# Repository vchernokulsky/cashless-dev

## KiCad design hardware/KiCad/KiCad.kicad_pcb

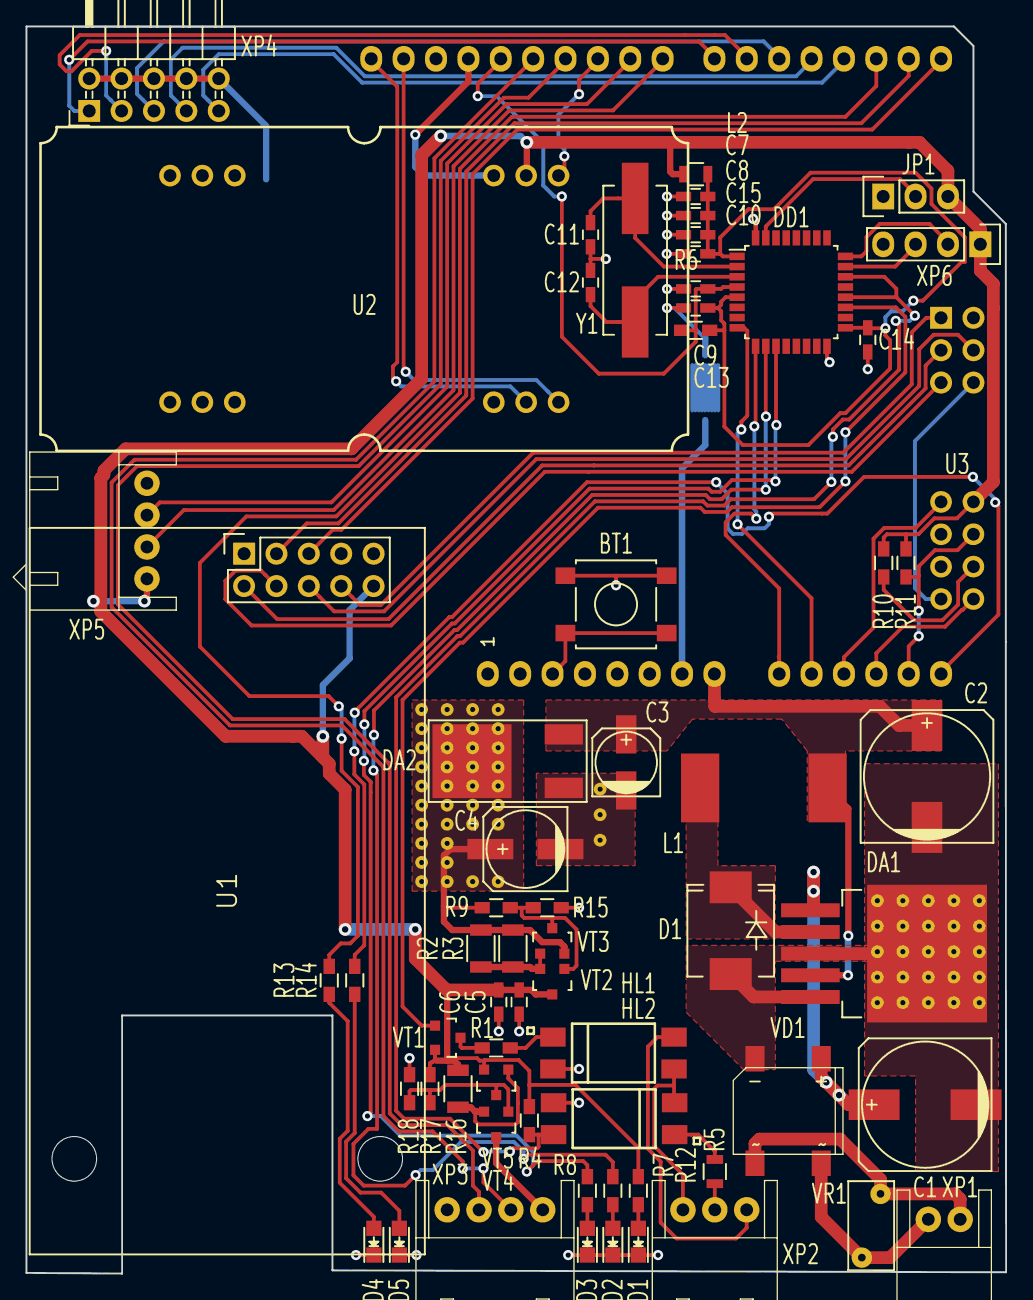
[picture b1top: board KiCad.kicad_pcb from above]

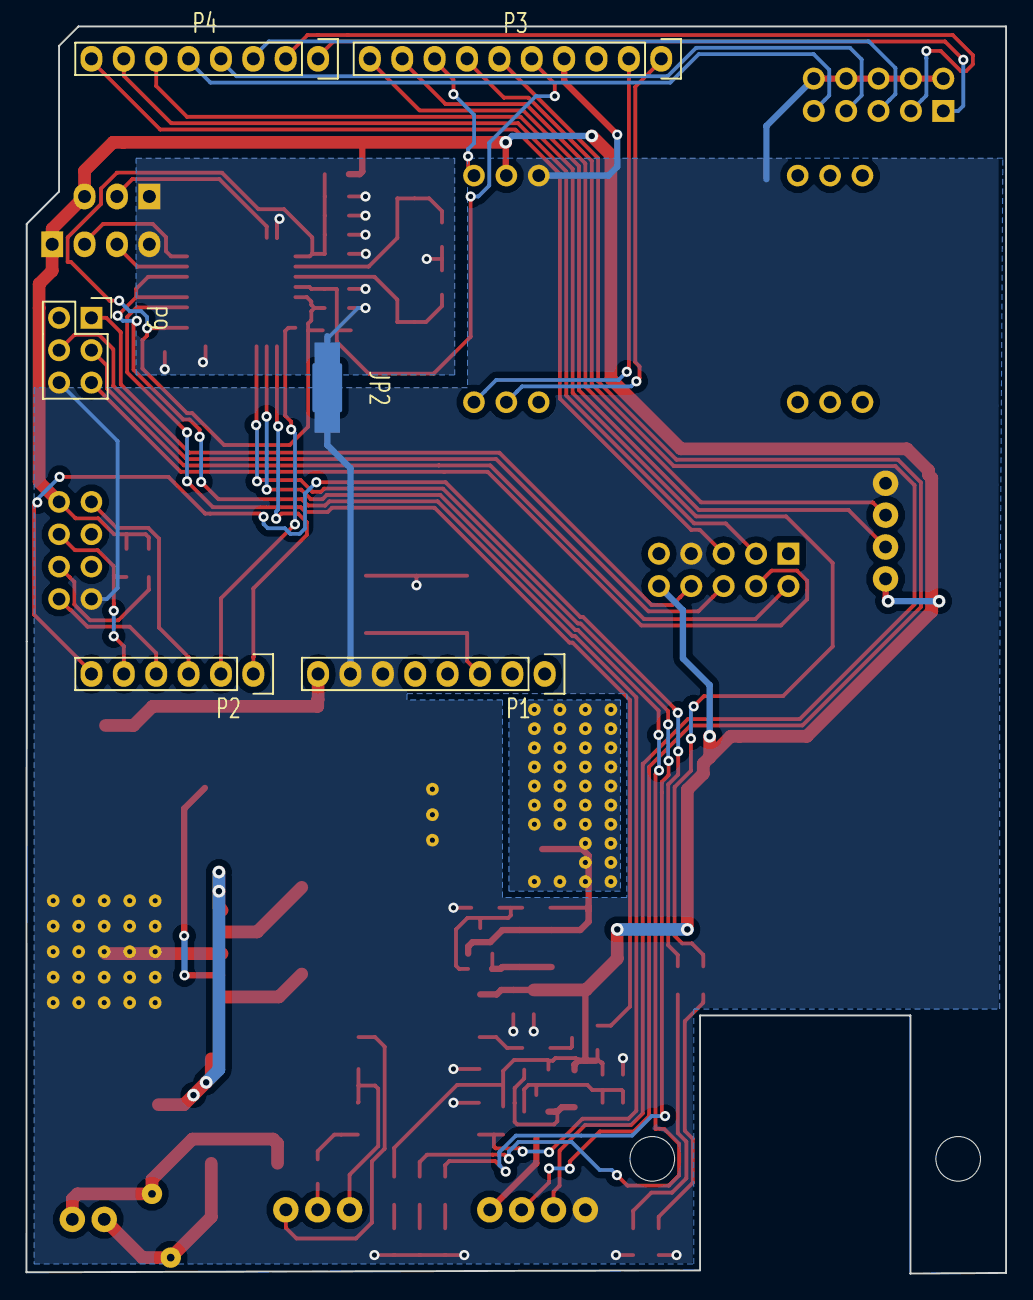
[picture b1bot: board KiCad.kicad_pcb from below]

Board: 2 copper layers, 76.9 x 97.8 mm, 71 parts (6 on the bottom side), 63 nets.

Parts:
BT1: RESET; SW_SPST_B3S-1000
C1: 100uF x 50V; c_elec_10x10
C2: 330uFx25V; c_elec_10x10
C3: 10uF x 25V; c_elec_5x5.3
C4: 100uF x10V; c_elec_6.3x7.7
C5, C8, C9, C10, C13, C14: 100nF x 6V3; C_0603_HandSoldering
C6, C7: 2.2uF x 6V3; C_0603_HandSoldering
C11, C12: 27pF; C_0603_HandSoldering
C15: 4.7uF x 6V3; C_0603_HandSoldering
D1: STPS3L60S; SMC_Standard
DA1: LM2575HVS-12; TO-263-5Lead
DA2: LD1086DT33TR; DPACK
DD1: STM32F042K6T6; LQFP-32_7x7mm_Pitch0.8mm
HL1, HL2: LTV-817S; DIP-4-SMD
JP1: BOOT MODE; Pin_Header_Straight_1x03
JP2: Jumper_NC_Small; NetTie-I_Connected_SMD
L1: 330 uH; CDRH127
L2: 220@100Mhz; R_0805
LD1, LD2: KP-2012SGC; LED-0805
LD3: KP-2012EC; LED-0805
LD4: KP-2012QBC-D; LED-0805
LD5: KP-2012SYC; LED-0805
P1: Power; Socket_Strip_Arduino_1x08
P2: Analog; Socket_Strip_Arduino_1x06
P3: Digital; Socket_Strip_Arduino_1x10
P4: Digital; Socket_Strip_Arduino_1x08
P9: PBD-6; Socket_Strip_Straight_2x03
R1: 120; R_0603_HandSoldering
R2, R3: 0.2; R_1206
R4: 1k; R_0603_HandSoldering
R5: 220; R_0805
R6, R9, R10, R11, R15, R17, R18: 10k; R_0603_HandSoldering
R7, R8, R14: 240; R_0603_HandSoldering
R12: 430; R_0603_HandSoldering
R13: 100; R_0603_HandSoldering
R16: 1 1%; R_1206
U1: W5500-SHIELD; Ethernet-Shield
U2: NFC-SHIELD
U3: ESP8266-01
VD1: DF01S
VR1: B72220S0300K101; RV_Disc_D7_W3.6_P5
VT1: PDTA114E.215; SOT-23
VT2, VT3, VT4, VT5: IRLML6401; SOT-23
XP1: CWF-2R
XP2: CWF-3R
XP3, XP5: CWF-4R
XP4: PLD-10R; Pin_Header_Angled_2x05
XP6: PBS-4; Socket_Strip_Straight_1x04
Y1: 8 MHz; Crystal_HC49-SD_SMD

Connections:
+3V3: C5.1, C6.1, JP1.3, L2.1, R4.2, R10.1, R11.1, R12.1, R16.1, R17.2, U1.10, U2.2, U3.8, VT1.2, VT2.3, VT5.2, XP5.1, XP6.1
DEBUG-RX: P3.9, XP5.3
DEBUG-TX: P3.10, XP5.2
ETH-INT: P4.7, U1.3
ETH-MISO: P9.1, U1.8
ETH-MOSI: P9.4, U1.6
ETH-RST: P4.8, U1.5
ETH-SCLK: P9.3, U1.2
ETH-SCS: P9.5, U1.4
GND: BT1.2, C1.2, C2.2, C3.2, C4.2, C5.2, C6.2, D1.2, DA1.3, DA1.5, DA2.1, HL1.2, HL2.3, JP2.1, LD1.1, LD2.1, LD3.1, LD4.1, LD5.1, P1.6, P1.7, P3.4, P9.6, R15.1, R18.1, U1.7, U2.3, U3.1, VD1.1, XP3.4, XP4.2, XP4.4, XP4.6, XP4.8, XP4.10, XP5.4
GNDREF: C7.2, C8.2, C9.1, C10.2, C11.2, C12.2, C13.2, C14.2, C15.2, DD1.16, DD1.32, JP1.1, JP2.2, XP6.4
GPIO-1: P4.1, XP4.1
GPIO-2: P4.2, XP4.3
GPIO-3: P4.3, XP4.5
GPIO-4: P4.4, XP4.7
GPIO-5: P4.5, XP4.9
I2C1-SCL: P3.1, U2.5
I2C1-SDA: P3.2, U2.4
I2C3-SCL: P3.6, XP3.2
I2C3-SDA: P3.7, XP3.3
LD-LINK: P4.6, R13.1
LD-MDB-RX: DD1.10, R7.1
LD-MDB-TX: DD1.11, R8.1
LD-SERVICE: P2.6, R14.1
MDB-RX: DD1.9, P2.1
MDB-TX: DD1.8, P2.2
MDBBUS-RX: DD1.20, DD1.22, HL2.4, R4.1
MDBBUS-TX: DD1.19, VT1.1
unnamed: C1.1, DA1.1, VD1.3
unnamed: C4.1, DA2.2, R2.1, R3.1, R9.2, VT3.2
unnamed: C11.1, DD1.2, Y1.1
unnamed: C12.1, DD1.3, Y1.2
unnamed: D1.1, DA1.2, L1.1
unnamed: DD1.31, JP1.2
unnamed: HL1.1, R1.2
unnamed: HL1.3, HL2.2, XP2.3
unnamed: HL1.4, XP2.1
unnamed: HL2.1, R5.1
unnamed: LD1.2, R12.2
unnamed: LD2.2, R7.2
unnamed: LD3.2, R8.2
unnamed: LD4.2, R13.2
unnamed: LD5.2, R14.2
unnamed: R1.1, VT1.3
unnamed: R2.2, R3.2, VT2.2, VT3.1
unnamed: R5.2, XP2.2
unnamed: R10.2, U3.4
unnamed: R9.1, R15.2, VT2.1, VT3.3
unnamed: R16.2, VT4.2, VT5.1
unnamed: R17.1, R18.2, VT4.1, VT5.3
unnamed: VD1.2, VR1.1, XP1.1
unnamed: VD1.4, VR1.2, XP1.2
unnamed: VT4.3, XP3.1
SWCLK: DD1.24, XP6.2
SWDDAT: DD1.23, XP6.3
VDD: C7.1, C8.1, C10.1, C13.1, C14.1, C15.1, DD1.1, DD1.5, DD1.17, L2.2, R6.1
VIN: C2.1, C3.1, DA1.4, DA2.3, L1.2, P1.8
WIFI-RX: P2.3, U3.7
WIFI-TX: P2.4, U3.2
~MDB-RES: C9.2, DD1.4, P3.5, R6.2
~NFC-INT: P3.8, U2.1
~RESET: BT1.1, P1.3
~WIFI-RES: P2.5, R11.2, U3.6

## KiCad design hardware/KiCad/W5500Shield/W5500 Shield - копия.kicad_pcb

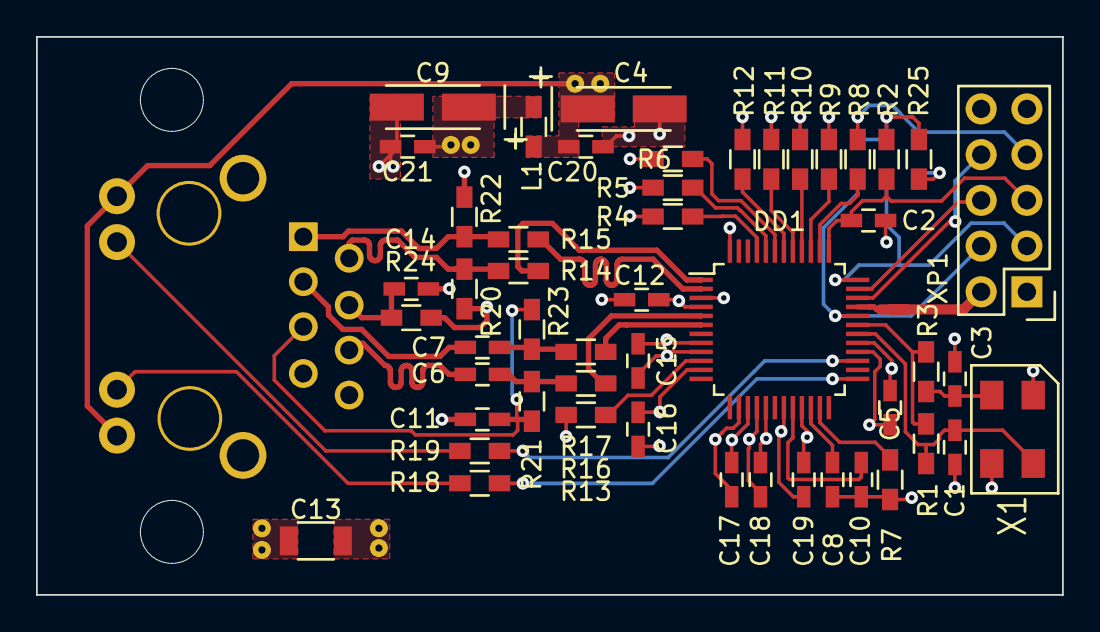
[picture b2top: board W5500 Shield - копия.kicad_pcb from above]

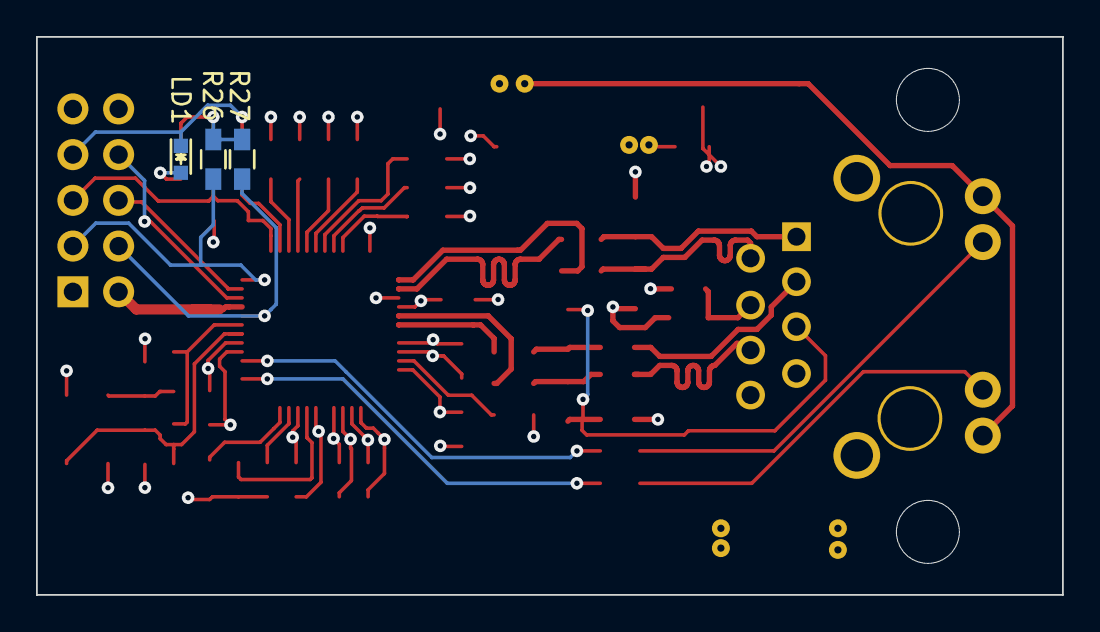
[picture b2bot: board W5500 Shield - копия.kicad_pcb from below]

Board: 4 copper layers, 57.0 x 31.0 mm, 54 parts (3 on the bottom side), 42 nets.

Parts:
C1, C3: 18 pF; C_0603_HandSoldering
C2, C5, C12, C15, C16, C17, C18, C19, C20, C21: 100nF; C_0603_HandSoldering
C4, C9: 10uF/16V; TantalC_SizeA_EIA-3216_HandSoldering
C6, C7: 6.8nF; C_0603_HandSoldering
C8, C11: 10nF; C_0603_HandSoldering
C10: 4.7uF; C_0603_HandSoldering
C13: 1nF/2kV; C_1206
C14: 22nF; C_0603_HandSoldering
DD1: W5500; LQFP-48_7x7mm_Pitch0.5mm
L1: 1000 @ 100Mhz; R_0603_HandSoldering
LD1: KP-1608SGC; LED_0603
P1: HR911105A; HR911105
R1: 1M; R_0603_HandSoldering
R2, R4, R5, R6, R7, R8, R9, R10, R11, R12, R26, R27: 10k; R_0603_HandSoldering
R3: 0R; R_0603_HandSoldering
R13: 12.4k 1%; R_0603_HandSoldering
R14, R15, R16, R17: 33R; R_0603_HandSoldering
R18, R19, R25: 330R; R_0603_HandSoldering
R20, R21, R22, R23: 49R9 1%; R_0603_HandSoldering
R24: 10R 1%; R_0603_HandSoldering
X1: 25 MHz; ABM3C
XP1: PLD-10; Pin_Header_Straight_2x05

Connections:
+3V3A: C9.1, C12.1, C15.1, C16.1, C17.1, C18.1, C19.1, C21.1, DD1.4, DD1.8, DD1.11, DD1.15, DD1.17, DD1.21, L1.2, R20.1, R22.1, R24.1
+3V3D: C4.1, C5.1, C20.1, DD1.28, L1.1, P1.9, P1.12, R2.2, R4.1, R5.1, R6.1, R25.1, R26.2, R27.2, XP1.10
/RX+: C7.2, P1.3
/RX-: C6.2, P1.6
/RX_N: DD1.5, R16.1
/RX_P: DD1.6, R17.1
/TX+: P1.1, R15.2, R22.2
/TX-: P1.2, R14.2, R20.2
/TX_N: DD1.1, R14.1
/TX_P: DD1.2, R15.1
ACTLED: P1.10, R19.2
Earth: C13.2, P1.0, P1.8
GND: C1.2, C2.2, C3.2, C4.2, C5.2, C8.2, C9.2, C10.2, C11.2, C12.2, C13.1, C14.2, C15.2, C16.2, C17.2, C18.2, C19.2, C20.2, C21.2, DD1.3, DD1.9, DD1.14, DD1.16, DD1.19, DD1.29, DD1.48, LD1.1, R7.1, R8.1, R9.1, R10.1, R11.1, R12.1, R13.2, X1.2, XP1.7
LINKLED: P1.11, R18.2
MISO: DD1.34, XP1.8
MOSI: DD1.35, XP1.6
unnamed: C1.1, DD1.30, R1.1, X1.1
unnamed: C3.1, R3.2, X1.3
unnamed: C6.1, R16.2, R21.1
unnamed: C7.1, R17.2, R23.1
unnamed: C8.1, DD1.22
unnamed: C10.1, DD1.20
unnamed: C11.1, P1.5, R21.2, R23.2
unnamed: C14.1, P1.4, R24.2
unnamed: DD1.10, R13.1
unnamed: DD1.23, R7.2
unnamed: DD1.25, R18.1
unnamed: DD1.27, R19.1
unnamed: DD1.31, R1.2, R3.1
unnamed: DD1.38, R8.2
unnamed: DD1.39, R9.2
unnamed: DD1.40, R10.2
unnamed: DD1.41, R11.2
unnamed: DD1.42, R12.2
unnamed: DD1.43, R6.2
unnamed: DD1.44, R5.2
unnamed: DD1.45, R4.2
unnamed: LD1.2, R25.2
SCLK: DD1.33, XP1.2
~INT: DD1.36, R26.1, XP1.3
~RES: C2.1, DD1.37, R2.1, XP1.5
~SCS: DD1.32, R27.1, XP1.4

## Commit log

2016-06-24 commit documentation
2016-06-24 espruino sketches commited
2016-06-24 doc changes
2016-06-27 PoC projects
2016-06-27 logIn() and getState() committed
2016-06-28 Refactoring: extract CPP protocol to new class
2016-06-28 accumulate card data behavior
2016-06-28 refactoring
2016-06-28 nfc and http cooperation (receive cash balance)
2016-06-28 simple changes
2016-06-28 changes in serial sketch
2016-06-28 small changes
2016-06-28 change logic in main.js
2016-06-30 Some changes in ExecMocup (29.06) and Forming nibbles to send (without sending)
2016-06-30 Simple changes in main.js
2016-07-02 Sending nibbles to Executive implemented
2016-07-04 project structure reorganization
2016-07-04 MDB protocol documentation
2016-07-04 ignore changes
2016-07-05 espruino part reorganize
2016-07-07 MDB sniffer for commands: RESET, SETUP
2016-07-07 fixes
2016-07-07 changes in PC test application
2016-07-07 Added structures for storing information about SETUP command
2016-07-07 extend sniffer behavior
2016-07-08 1. Extract command build behavior to module 2. Extract VMC settings setup to module
2016-07-08 fix bug in MDBCmdParser module
2016-07-09 implement correct vend session
2016-07-09 FIX startup sequence errors
2016-07-09 Correct vend session debugged (scenario on p.169)
2016-07-11 UID to content
2016-07-11 Scenarios on p. 171, 172, 173 implemented
2016-07-13 mbd transport layer
2016-07-13 extract logger function
2016-07-14 Scenario on p. 174 is ready
2016-07-14 refactoring for use C compilerr
2016-07-14 add function for testing single vend session
2016-07-14 refactoring in output logger
2016-07-14 "Valid Single Vend" for transport layer
2016-07-14 include sources for MIC
2016-07-14 add STM spec files
2016-07-15 WiFi module sketch
2016-07-15 LOGIC & TRANSPORT communication
2016-07-16 VMC mockup for PowerUp and VendSuccess sequences
2016-07-16 fix bugs in TRANSPORT <-> LOGIC communications
2016-07-16 simple changes in project structure
2016-07-17 fixes in VMC mockup
2016-07-17 eclipse project setup
2016-07-18 code reorganization
2016-07-18 change TRANSPORT <-> LOGIC protocol
2016-07-18 simple refactoring
2016-07-18 log for STM32 platform
2016-07-19 change SESSION IDLE state behavior
2016-07-19 vend behavior implementation
2016-07-22 Record Chipid (in Array form) on pages 3-4. Reading all pages for check
2016-07-22 Reading chipid from RFID (pages 4-5), sending two requests to http (get and set (pressed BTN1) balance value)
2016-07-25 Fixes in write/read chipid from rfid
2016-07-28 changes for protopyping
2016-07-28 mifare classic read
2016-07-29 Mifare Classic behavior
2016-08-01 fix problem with reading mifare classic after authentication error
2016-08-01 ignore binary docs
2016-08-03 changes in NFC library
2016-08-03 remove unused scripts
2016-08-03 change MDB transport commands
2016-08-03 reading ChipId from mifare classic card
2016-08-03 project config for STM F040
2016-08-03 simple fixes
2016-08-04 extend log info
2016-08-05 session timeout behavior
2016-08-06 simple fixes in espruino code
2016-08-06 changes in log messages for better subcommand understanding
2016-08-06 function for read espruino ready command
2016-08-06 timeout in 5s for waiting espruino board
2016-08-06 ignore some local files
2016-08-07 change logging to USART (Serial2)
2016-08-07 vend session indication on NUCLEO
2016-08-11 binary protocol behavior
2016-08-11 changes in test VS project file
2016-08-11 simple changes in test VS project
2016-08-16 GloLime protocol
2016-08-17 Fixes in GloLime
2016-08-17 MDB protocol changes
2016-08-17 remove unused files
2016-08-17 change mdb <--> espruino communication protocol
2016-08-17 renaming
2016-08-17 new ignores
2016-08-18 GloLime protocol integration
2016-08-23 fix device initialization
2016-08-23 behavior changes for STM042
2016-08-25 change SportLife vend behavior
2016-08-25 send ItemId to espruino
2016-08-25 new ignore rules
2016-08-25 include internal docs
2016-08-28 last changes
2016-08-28 some changes in main
2016-08-28 Check writeOffId and some changes in main
2016-08-29 Fixes in GloLime main
2016-08-29 Detection additional "Error" added (Command Exit Codes for Glo Lime response)
2016-09-03 Some changes and fixes in "mains"
2016-09-07 revalue behavior added
2016-09-09 fixes in mains
2016-09-09 simple fixeses
2016-09-11 glolime main fixes
2016-09-12 some fixes for glolime main
2016-09-12 touchbox IP added in glolime main
2016-09-14 glolime fixes
2016-09-15 File for test ethernet
2016-09-15 change led behavior
2016-09-15 change to static network configuration
2016-09-15 changes in LED behavior
2016-09-15 ignores
2016-09-15 fix bug with approve vend always
2016-09-16 socket stress-test
2016-09-17 check user session
2016-09-17 fix bad session start
2016-09-18 refactoring: checking current sessionId in HTTP communication
2016-09-18 add reboot behaviour
2016-09-20 last fixes
2016-09-20 fixes in SL-main
2016-09-20 network failures calculation
2016-09-20 fix network timeout behaviour
2016-09-21 fix bug with cyclic buffer reading
2016-09-22 cosmetic fixes for schools
2016-09-23 LED indication behaviour
2016-09-25 balance correctness check was add
2016-09-26 fixes for internal communications
2016-09-26 last fixes with for SportLife
2016-09-30 module for CRC16 (not tested!)
2016-10-05 Some changes in crc-module
2016-10-05 crc16-module for testing
2016-10-05 js-file for test CRC16-module
2016-10-05 fix bug in CRC16 module
2016-10-05 repo reorganisation
2016-10-05 refactoring to code minimisation
2016-10-05 led blink carousel
2016-10-05 Reading NetworkConfig from Flash-memory
2016-10-12 config info in JSON (UART communication test)
2016-10-12 Transfer config info by UART
2016-10-26 Network config by bluetooth connection
2016-10-26 fixes in bluetooth configuration
2016-10-27 UART file settings
2016-11-08 firmware without config
2016-11-25 Add Hardaware Files for Cashless Device
2016-11-29 hotfix
2016-12-07 check negative value
2016-12-13 negative balance check
2016-12-21 upd gitignore commit
2016-12-21 refactoring (CommGlolime module)
2016-12-28 extract network configuration
2017-01-04 extract network configuration from main.js
2017-01-04 create public glolime API
2017-01-06 getBalance behaviour extracted
2017-01-09 integrate product sell behavior
2017-01-09 connection configurator and glolime modules
2017-01-09 fixes in glolime module and logic
2017-01-19 fixes in network config setup
2017-01-20 #8 standalone modules
2017-01-20 #4 extract indication
2017-01-20 simple fixes in indications
2017-01-20 #1 added event behavior
2017-01-20 little endian fixes
2017-01-20 add network config store FIX: problem with balance conversion
2017-01-23 code reorganise
2017-01-23 add PING utility for standalone flash operation
2017-04-05 commit STM platform libs
2017-04-05 commit main logic
2017-04-05 commit new ignores
2018-08-15 partly reorganized
2018-08-15 reorganize
